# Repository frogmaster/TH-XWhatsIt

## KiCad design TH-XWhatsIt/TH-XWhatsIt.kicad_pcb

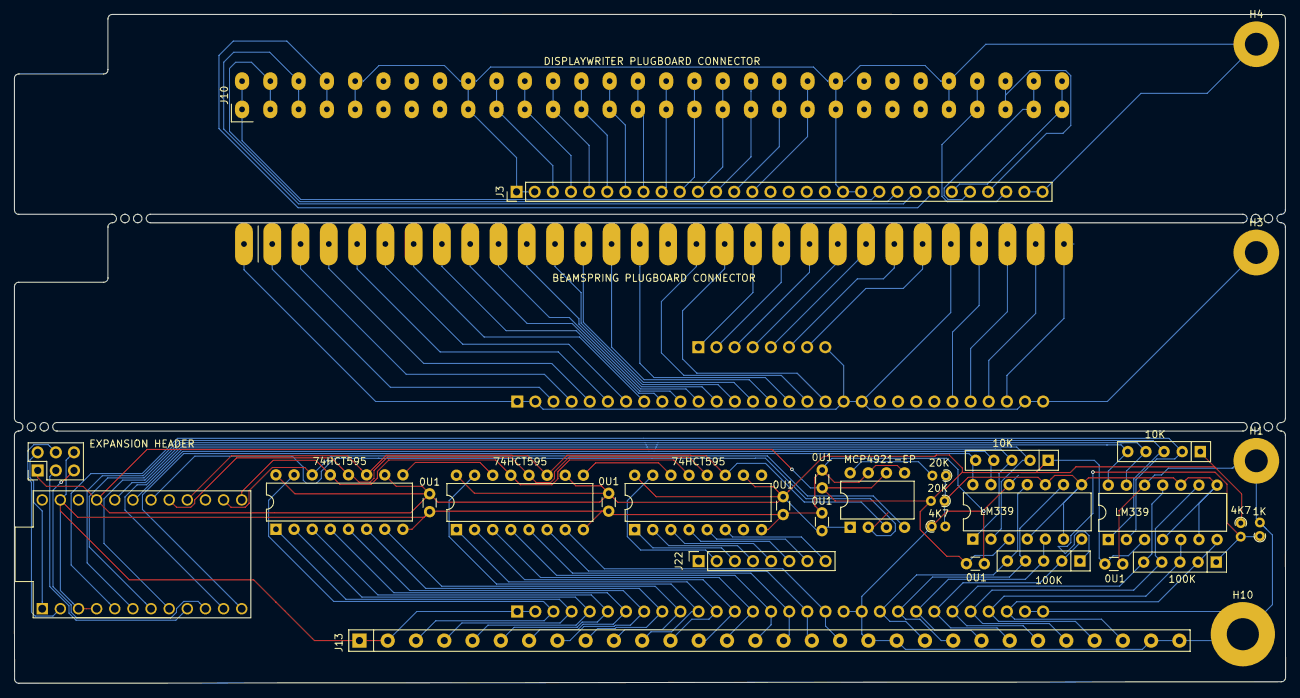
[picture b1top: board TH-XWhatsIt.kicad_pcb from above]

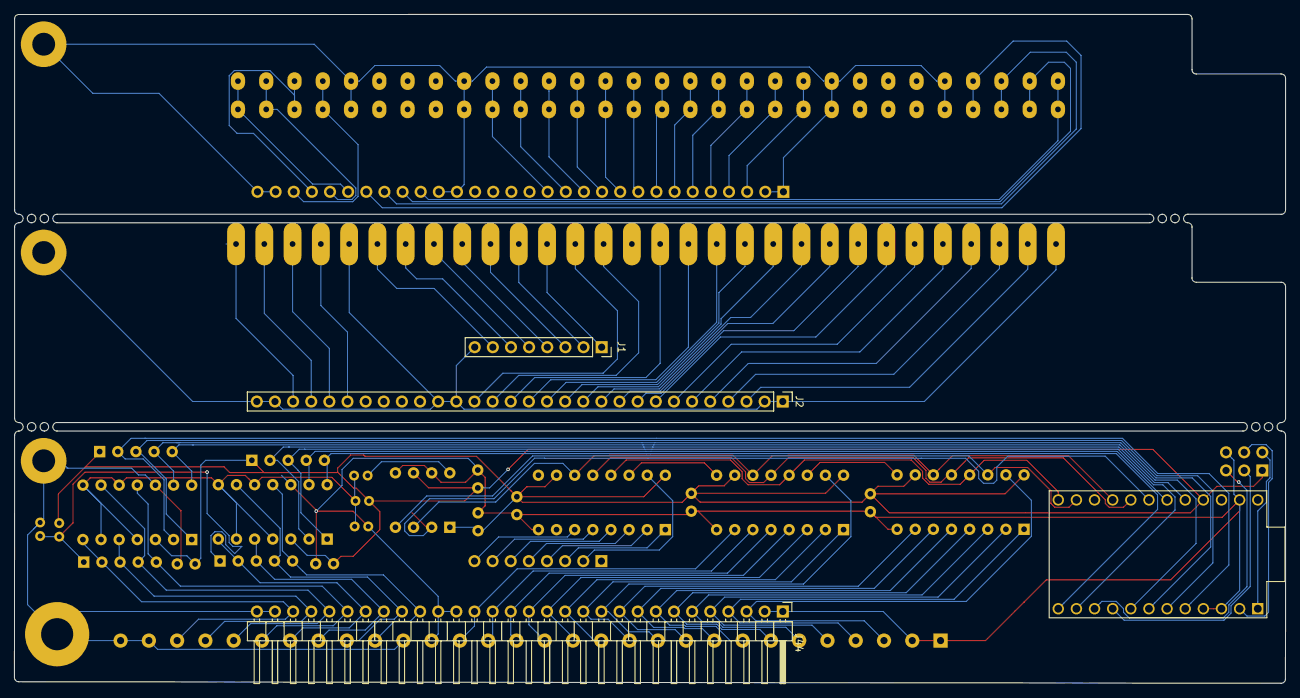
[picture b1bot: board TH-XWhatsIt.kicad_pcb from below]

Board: 2 copper layers, 178.0 x 93.7 mm, 36 parts (3 on the bottom side), 104 nets.

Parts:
C3, C4, C5, C7, C8, C9, C10: 0U1; C_Disc_D3.0mm_W1.6mm_P2.50mm
H1, H3, H4: GROUND STRAP; MountingHole_3.2mm_M3_Pad
H10: GROUND STRAP; MountingHole_4.5mm_Pad
J1: Conn_01x08; PinSocket_1x08_P2.54mm_Vertical
J2, J3: MODEL F PLUGBOARD CONNECTOR; PinHeader_1x30_P2.54mm_Vertical
J7: BEAMSPRING PLUGBOARD CONNECTOR; 3..6mm_cardedge
J10: DISPLAYWRITER PLUGBOARD CONNECTOR; DIP-60_155_ELL
J12: EXPANSION HEADER; PinHeader_2x03_P2.54mm_Vertical
J13: Model F AT; SIP-30-P3.96
J22: Beamsring extra; PinSocket_1x08_P2.54mm_Vertical
J44: Model F or Plugboard; PinHeader_1x30_P2.54mm_Horizontal
R1, R5: 4K7; R_Axial_DIN0204_L3.6mm_D1.6mm_P1.90mm_Vertical
R2: 1K; R_Axial_DIN0204_L3.6mm_D1.6mm_P1.90mm_Vertical
R3, R4: 20K; R_Axial_DIN0204_L3.6mm_D1.6mm_P1.90mm_Vertical
RN1, RN3: 100K; R_Array_SIP5
RN2, RN4: 10K; R_Array_SIP5
U1, U6: LM339; DIP-14_W7.62mm
U2: MCP4921-EP; DIP-8_W7.62mm
U3, U5, U8: 74HCT595; DIP-16_W7.62mm
U7: ProMicro

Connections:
+5VA: C3.2, C4.2, C5.2, C7.2, C8.2, C9.2, C10.2, J12.1, R1.1, R3.2, RN2.1, RN4.1, U1.3, U2.1, U2.6, U3.10, U3.16, U5.10, U5.16, U6.3, U7.21, U8.10, U8.16
/beamspring plugboard/BSCOL1: J2.3, J7.2
/beamspring plugboard/BSCOL2: J2.4, J7.3
/beamspring plugboard/BSCOL3: J2.5, J7.4
/beamspring plugboard/BSCOL4: J2.6, J7.5
/beamspring plugboard/BSCOL5: J2.7, J7.6
/beamspring plugboard/BSCOL6: J2.8, J7.7
/beamspring plugboard/BSCOL7: J2.9, J7.8
/beamspring plugboard/BSCOL8: J2.10, J7.9
/beamspring plugboard/BSCOL9: J2.11, J7.10
/beamspring plugboard/BSCOL10: J2.12, J7.11
/beamspring plugboard/BSCOL11: J2.13, J7.12
/beamspring plugboard/BSCOL12: J2.14, J7.13
/beamspring plugboard/BSCOL13: J2.15, J7.14
/beamspring plugboard/BSCOL14: J2.16, J7.15
/beamspring plugboard/BSCOL15: J2.17, J7.17
/beamspring plugboard/BSCOL16: J2.18, J7.18
/beamspring plugboard/BSCOL17: J1.1, J7.19
/beamspring plugboard/BSCOL18: J1.2, J7.20
/beamspring plugboard/BSCOL19: J1.3, J7.21
/beamspring plugboard/BSCOL20: J1.4, J7.22
/beamspring plugboard/BSCOL21: J1.5, J7.23
/beamspring plugboard/BSCOL22: J1.6, J7.24
/beamspring plugboard/BSCOL23: J1.7, J7.25
/beamspring plugboard/BSGROUND: H3.1, J1.8, J2.1, J2.2, J2.19, J2.20, J2.29, J2.30, J7.1, J7.26
/beamspring plugboard/BSSENSE1: J2.25, J7.27
/beamspring plugboard/BSSENSE2: J2.26, J7.28
/beamspring plugboard/BSSENSE3: J2.27, J7.29
/beamspring plugboard/BSSENSE4: J2.28, J7.30
/displaywriter plugboard/DWCOL1: J3.3, J10.10, J10.51
/displaywriter plugboard/DWCOL2: J3.4, J10.11, J10.50
/displaywriter plugboard/DWCOL3: J3.5, J10.12, J10.49
/displaywriter plugboard/DWCOL4: J3.6, J10.13, J10.48
/displaywriter plugboard/DWCOL5: J3.7, J10.14, J10.47
/displaywriter plugboard/DWCOL6: J3.8, J10.15, J10.46
/displaywriter plugboard/DWCOL7: J3.9, J10.16, J10.45
/displaywriter plugboard/DWCOL8: J3.10, J10.17, J10.44
/displaywriter plugboard/DWCOL9: J3.11, J10.18, J10.43
/displaywriter plugboard/DWCOL10: J3.12, J10.19, J10.42
/displaywriter plugboard/DWCOL11: J3.13, J10.20, J10.41
/displaywriter plugboard/DWCOL12: J3.14, J10.21, J10.40
/displaywriter plugboard/DWGROUND: H4.1, J3.1, J3.2, J3.19, J3.20, J3.29, J3.30, J10.5, J10.9, J10.22, J10.26, J10.35, J10.39, J10.52, J10.56
/displaywriter plugboard/DWSENSE1: J3.21, J10.1, J10.60
/displaywriter plugboard/DWSENSE2: J3.22, J10.2, J10.59
/displaywriter plugboard/DWSENSE3: J3.23, J10.3, J10.58
/displaywriter plugboard/DWSENSE4: J3.24, J10.4, J10.57
/displaywriter plugboard/DWSENSE5: J3.28, J10.27, J10.34
/displaywriter plugboard/DWSENSE6: J3.27, J10.28, J10.33
/displaywriter plugboard/DWSENSE7: J3.26, J10.29, J10.32
/displaywriter plugboard/DWSENSE8: J3.25, J10.30, J10.31
CLOCK: U2.3, U3.11, U5.11, U7.16, U8.11
COL1: J13.3, J44.3, U3.15
COL2: J13.4, J44.4, U3.1
COL3: J13.5, J44.5, U3.2
COL4: J13.6, J44.6, U3.3
COL5: J13.7, J44.7, U3.4
COL6: J13.8, J44.8, U3.5
COL7: J13.9, J44.9, U3.6
COL8: J13.10, J44.10, U3.7
COL9: J13.11, J44.11, U5.15
COL10: J13.12, J44.12, U5.1
COL11: J13.13, J44.13, U5.2
COL12: J13.14, J44.14, U5.3
COL13: J13.15, J44.15, U5.4
COL14: J13.16, J44.16, U5.5
COL15: J13.17, J44.17, U5.6
COL16: J13.18, J44.18, U5.7
COL17: J22.2, U8.15
COL18: J22.3, U8.1
COL19: J22.4, U8.2
COL20: J22.5, U8.3
COL21: J22.6, U8.4
COL22: J22.7, U8.5
COL23: J22.8, U8.6
GNDA: C3.1, C4.1, C5.1, C7.1, C8.1, C9.1, C10.1, H1.1, H10.1, J12.6, J13.1, J13.2, J13.19, J13.20, J13.29, J13.30, J44.1, J44.2, J44.19, J44.20, J44.29, J44.30, R2.2, R5.1, U1.12, U2.5, U2.7, U3.8, U5.8, U6.12, U7.3, U7.4, U7.23, U8.8
HEADER1: J12.3, U7.9
HEADER2: J12.5, U7.10
HEADER3: J12.2, U7.1
HEADER4: J12.4, U7.2
LOADCOL: U3.12, U5.12, U7.17, U8.12
MOSI: U2.4, U3.14, U7.14
unnamed: R1.2, R2.1, RN1.1, RN3.1
unnamed: R4.2, U2.8
ROW1: RN2.3, U1.1, U7.6
ROW2: RN2.2, U1.2, U7.5
ROW3: RN2.5, U1.14, U7.8
ROW4: RN2.4, U1.13, U7.7
ROW5: RN4.3, U6.1, U7.11
ROW6: RN4.5, U6.14, U7.12
ROW7: RN4.2, U6.2, U7.20
ROW8: RN4.4, U6.13, U7.19
SENSE1: J13.28, J44.28, RN1.2, U1.7
SENSE2: J13.27, J44.27, RN1.3, U1.5
SENSE3: J13.26, J44.26, RN1.4, U1.9
SENSE4: J13.25, J44.25, RN1.5, U1.11
SENSE5: J13.24, J44.24, RN3.2, U6.7
SENSE6: J13.22, J44.22, RN3.4, U6.9
SENSE7: J13.23, J44.23, RN3.3, U6.5
SENSE8: J13.21, J44.21, RN3.5, U6.11
SERIALOUT1: U3.9, U5.14
SERIALOUT2: U5.9, U8.14
SETPOINT: R3.1, R4.1, R5.2, U1.4, U1.6, U1.8, U1.10, U6.4, U6.6, U6.8, U6.10
~OE: U3.13, U5.13, U7.13, U8.13
~SELECTDAC: U2.2, U7.18

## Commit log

2020-07-30 My try of adding model-f at support
2020-07-30 move stuff around near sense lines
2020-07-30 add back mistakenly deleted file
2020-07-30 don't track bak files
2020-07-30 moved to TH-XWatsit/lib_fp.pretty
2020-07-30 some more small fixes
2020-07-30 fix drc and unconnected networks
2020-07-30 add some dimensions to show changes
2020-07-30 silk fixes
2020-08-21 add preview pdf file

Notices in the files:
TH-XWhatsIt/TH-XWhatsIt.kicad_pcb:
Licenced under CERN OHL Version 1.2
Copyright Rainy Day Plans.
This documentation describes Open Hardware and is licensed under the
CERN OHL v. 1.2.
